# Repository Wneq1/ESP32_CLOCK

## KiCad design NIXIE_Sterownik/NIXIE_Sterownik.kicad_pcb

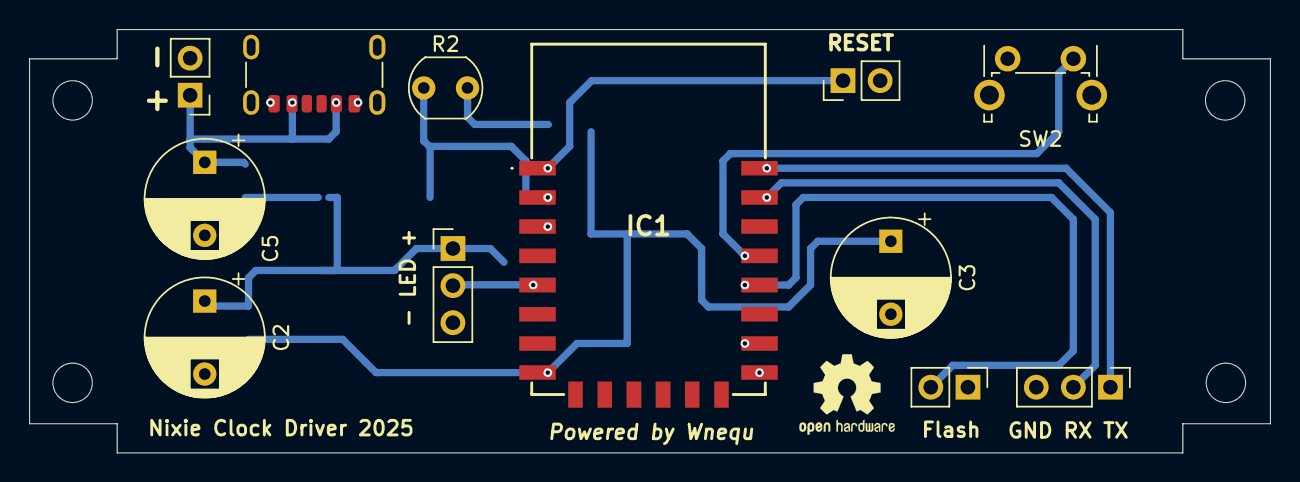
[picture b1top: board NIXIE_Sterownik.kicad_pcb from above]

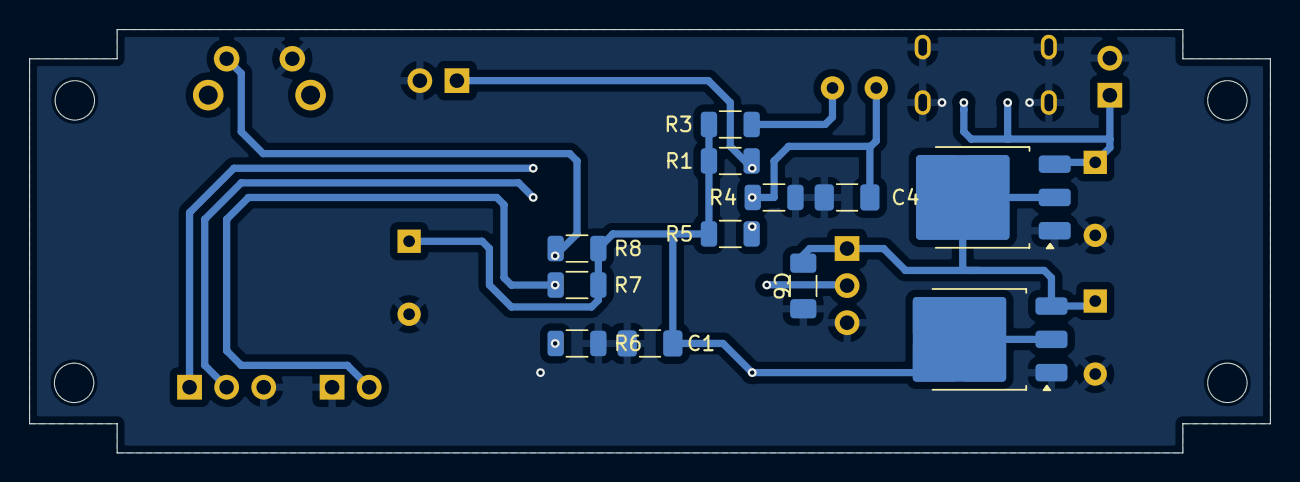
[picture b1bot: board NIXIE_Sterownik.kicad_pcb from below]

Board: 2 copper layers, 85.0 x 29.0 mm, 24 parts (12 on the bottom side), 14 nets.

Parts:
C1, C6: 100n; C_1206_3216Metric_Pad1.33x1.80mm_HandSolder
C2, C3, C5: 100u; CP_Radial_D8.0mm_P5.00mm
C4: 1uF; C_1206_3216Metric_Pad1.33x1.80mm_HandSolder
IC1: ESP12F
J1: VCC; PinHeader_1x02_P2.54mm_Vertical
J2: RESET; PinHeader_1x02_P2.54mm_Vertical
J3: LED; PinHeader_1x03_P2.54mm_Vertical
J4: FLASH; PinHeader_1x02_P2.54mm_Vertical
J5: USB_C_Receptacle_PowerOnly_6P; USB_C_Receptacle_GCT_USB4125-xx-x_6P_TopMnt_Horizontal
J6: PROGRAMMING; PinHeader_1x03_P2.54mm_Vertical
R1, R5, R6, R7, R8: 10k; R_1206_3216Metric
R2: GL5516; R_LDR_5.0x4.1mm_P3mm_Vertical
R3: 2k2; R_1206_3216Metric
R4: 4k7; R_1206_3216Metric
SW2: CHANGE; SW_Tactile_SPST_Angled_PTS645Vx83-2LFS
U1: LM1117DT-3.3; TO-252-3_TabPin2
U2: LM1117DT-5.0; TO-252-3_TabPin2

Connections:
+3.3V: C1.1, C3.1, IC1.8 (VCC), R1.1, R3.1, R5.1, R7.2, R8.2, U1.2 (VO)
+5V: C2.1, C6.1, J3.1, U1.3 (VI), U2.2 (VO)
ADC: C4.1, IC1.2 (ADC), R2.2, R4.1
CHANGE: IC1.19 (IO4), R8.1, SW2.2 (D)
GND: C1.2, C2.2, C3.2, C4.2, C5.2, C6.2, IC1.15 (GND), J1.2, J2.2, J3.3, J4.1, J5.A12 (GND), J5.B12 (GND), J5.S1 (SHIELD), J6.3, R4.2, R6.2, SW2.1 (C), U1.1 (GND), U2.1 (GND)
LED: IC1.5 (IO14), J3.2
unnamed: IC1.3 (EN), R5.2
unnamed: IC1.18 (IO0), J4.2, R7.1
unnamed: IC1.16 (IO15), R6.1
unnamed: IC1.1 (RST), J2.1, R1.2
unnamed: C5.1, J1.1, J5.A9 (VBUS), J5.B9 (VBUS), U2.3 (VI)
unnamed: R2.1, R3.2
RX: IC1.21 (RXD), J6.2
TX: IC1.22 (TXD), J6.1

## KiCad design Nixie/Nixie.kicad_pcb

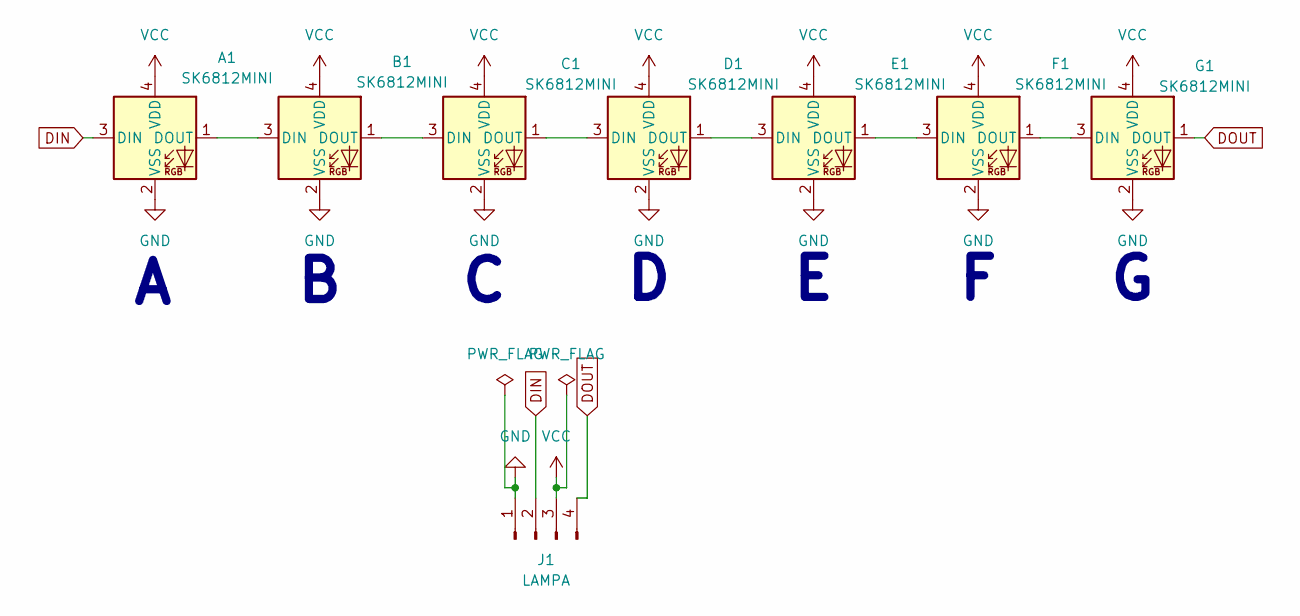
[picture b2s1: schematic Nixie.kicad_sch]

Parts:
A1: SK6812MINI; LED_SK6812MINI_PLCC4_3.5x3.5mm_P1.75mm
B1: SK6812MINI; LED_SK6812MINI_PLCC4_3.5x3.5mm_P1.75mm
C1: SK6812MINI; LED_SK6812MINI_PLCC4_3.5x3.5mm_P1.75mm
D1: SK6812MINI; LED_SK6812MINI_PLCC4_3.5x3.5mm_P1.75mm
E1: SK6812MINI; LED_SK6812MINI_PLCC4_3.5x3.5mm_P1.75mm
F1: SK6812MINI; LED_SK6812MINI_PLCC4_3.5x3.5mm_P1.75mm
G1: SK6812MINI; LED_SK6812MINI_PLCC4_3.5x3.5mm_P1.75mm
J1: LAMPA; PinHeader_1x04_P2.54mm_Horizontal

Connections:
DIN: A1.3 (DIN), J1.2
DOUT: G1.1 (DOUT), J1.4
GND: A1.2 (VSS), B1.2 (VSS), C1.2 (VSS), D1.2 (VSS), E1.2 (VSS), F1.2 (VSS), G1.2 (VSS), J1.1
unnamed: A1.1 (DOUT), B1.3 (DIN)
unnamed: B1.1 (DOUT), C1.3 (DIN)
unnamed: C1.1 (DOUT), D1.3 (DIN)
unnamed: D1.1 (DOUT), E1.3 (DIN)
unnamed: E1.1 (DOUT), F1.3 (DIN)
unnamed: F1.1 (DOUT), G1.3 (DIN)
VCC: A1.4 (VDD), B1.4 (VDD), C1.4 (VDD), D1.4 (VDD), E1.4 (VDD), F1.4 (VDD), G1.4 (VDD), J1.3

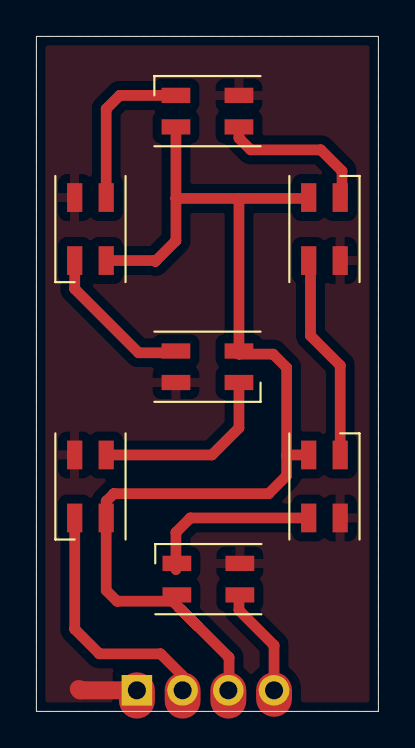
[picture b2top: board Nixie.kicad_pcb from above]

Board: 2 copper layers, 19.0 x 37.5 mm, 8 parts (1 on the bottom side), 10 nets.
